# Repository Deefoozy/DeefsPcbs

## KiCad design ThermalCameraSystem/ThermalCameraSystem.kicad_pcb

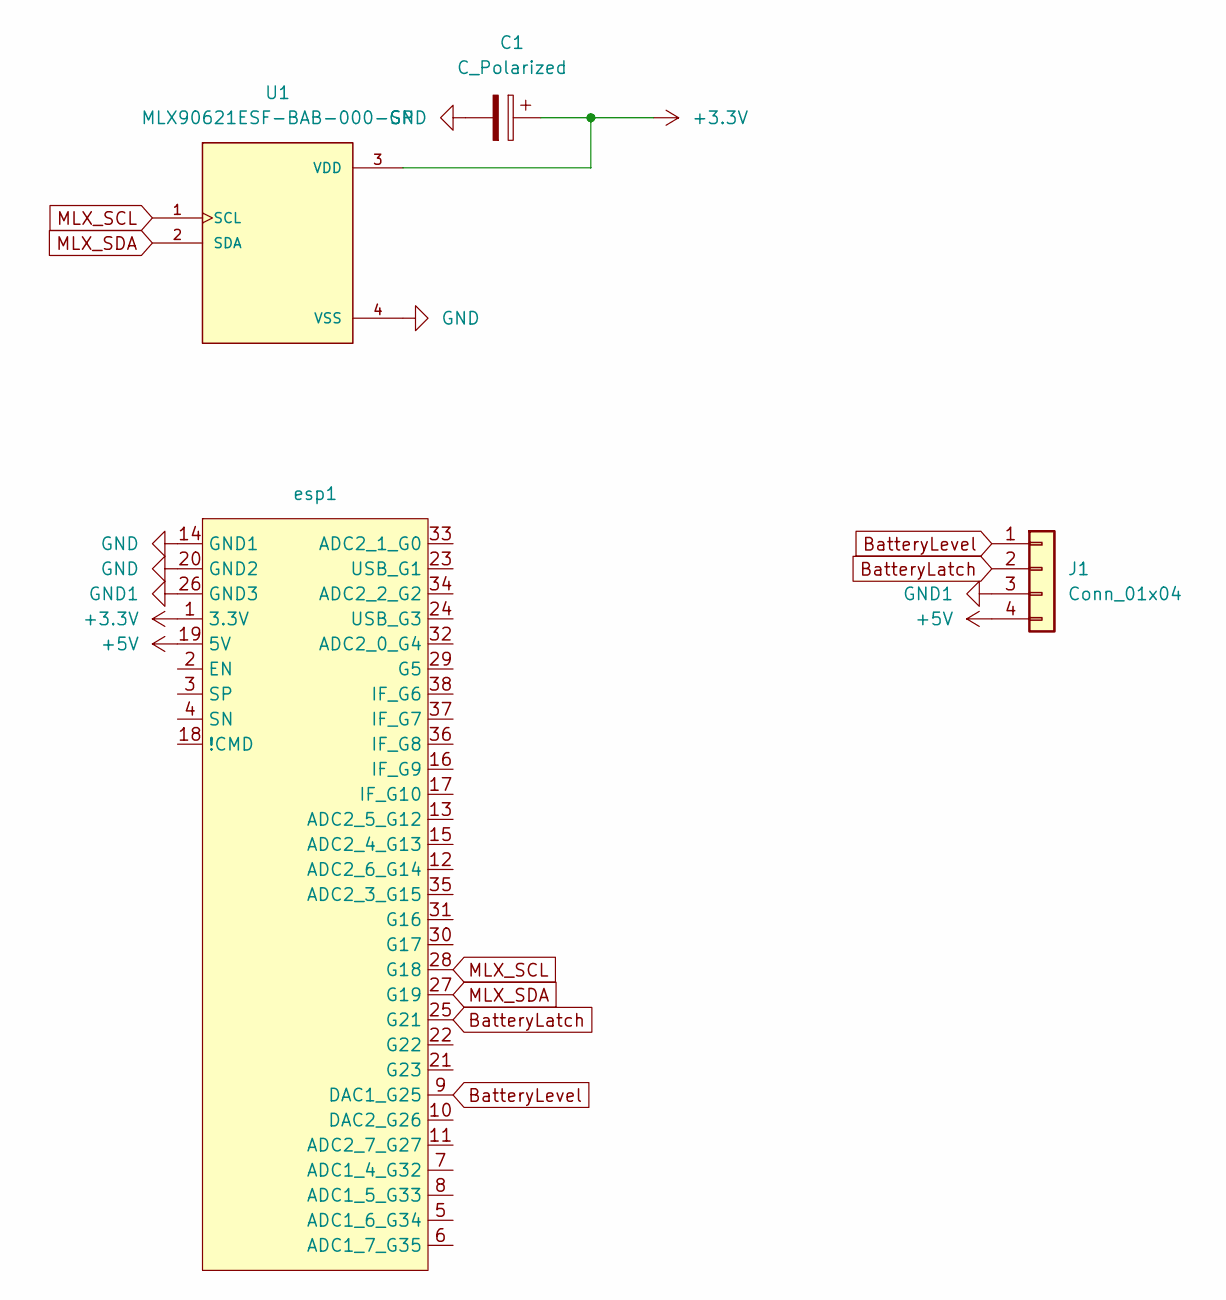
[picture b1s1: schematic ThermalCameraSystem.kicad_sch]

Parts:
C1: C_Polarized; C_Disc_D4.3mm_W1.9mm_P5.00mm
J1: Conn_01x04; PinSocket_1x04_P2.54mm_Vertical
U1: MLX90621ESF-BAB-000-SP; TO292P930H600-4
esp1: AZdelivery_nodemcu_esp32

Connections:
+3.3V: C1.1, U1.3 (VDD), esp1.1 (3.3V)
+5V: J1.4, esp1.19 (5V)
BatteryLatch: J1.2, esp1.25 (G21)
BatteryLevel: J1.1, esp1.9 (DAC1_G25)
GND: C1.2, U1.4 (VSS), esp1.14 (GND1), esp1.20 (GND2)
GND1: J1.3, esp1.26 (GND3)
MLX_SCL: U1.1 (SCL), esp1.28 (G18)
MLX_SDA: U1.2 (SDA), esp1.27 (G19)

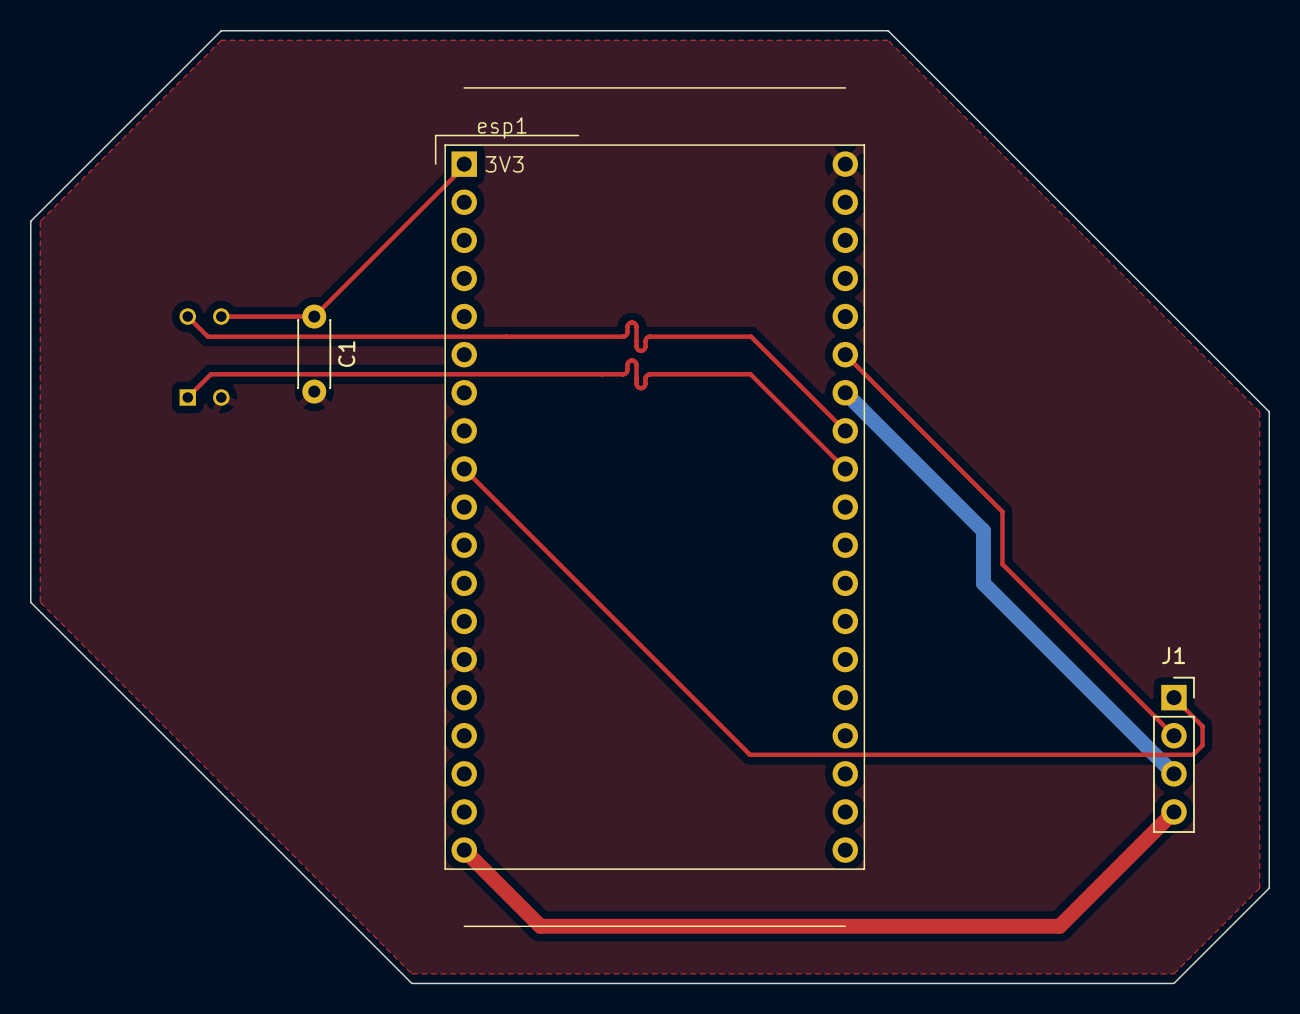
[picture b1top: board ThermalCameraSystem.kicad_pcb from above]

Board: 2 copper layers, 82.5 x 63.5 mm, 4 parts (1 on the bottom side), 8 nets.

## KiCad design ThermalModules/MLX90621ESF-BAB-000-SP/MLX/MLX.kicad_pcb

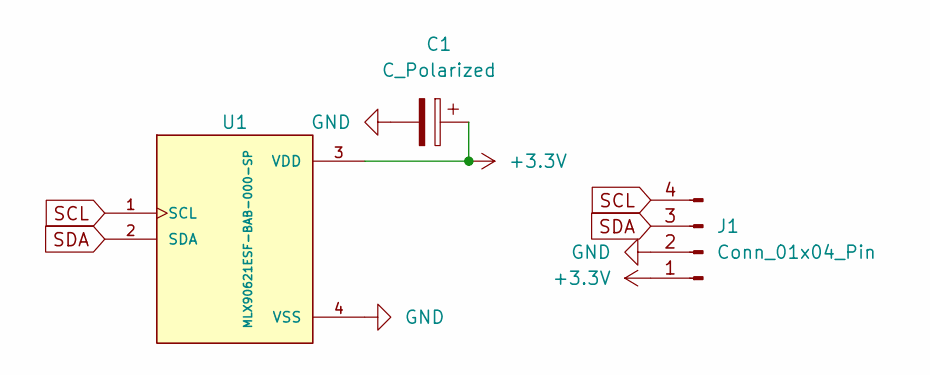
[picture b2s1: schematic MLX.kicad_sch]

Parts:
C1: C_Polarized; C_Disc_D4.3mm_W1.9mm_P5.00mm
J1: Conn_01x04_Pin; PinHeader_1x04_P2.54mm_Vertical
U1: MLX90621ESF-BAB-000-SP; TO254P940H1340-4

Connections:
+3.3V: C1.1, J1.1, U1.3 (VDD)
GND: C1.2, J1.2, U1.4 (VSS)
SCL: J1.4, U1.1 (SCL)
SDA: J1.3, U1.2 (SDA)

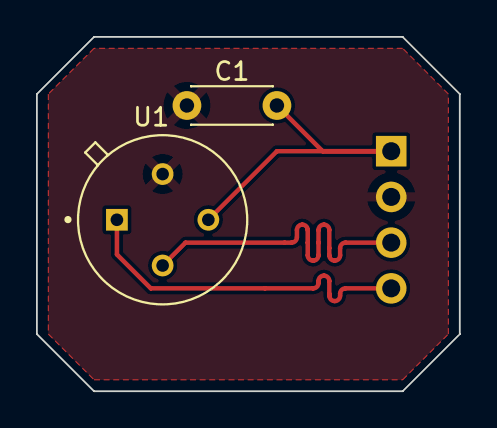
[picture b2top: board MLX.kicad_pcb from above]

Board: 2 copper layers, 23.5 x 19.7 mm, 3 parts (1 on the bottom side), 4 nets.

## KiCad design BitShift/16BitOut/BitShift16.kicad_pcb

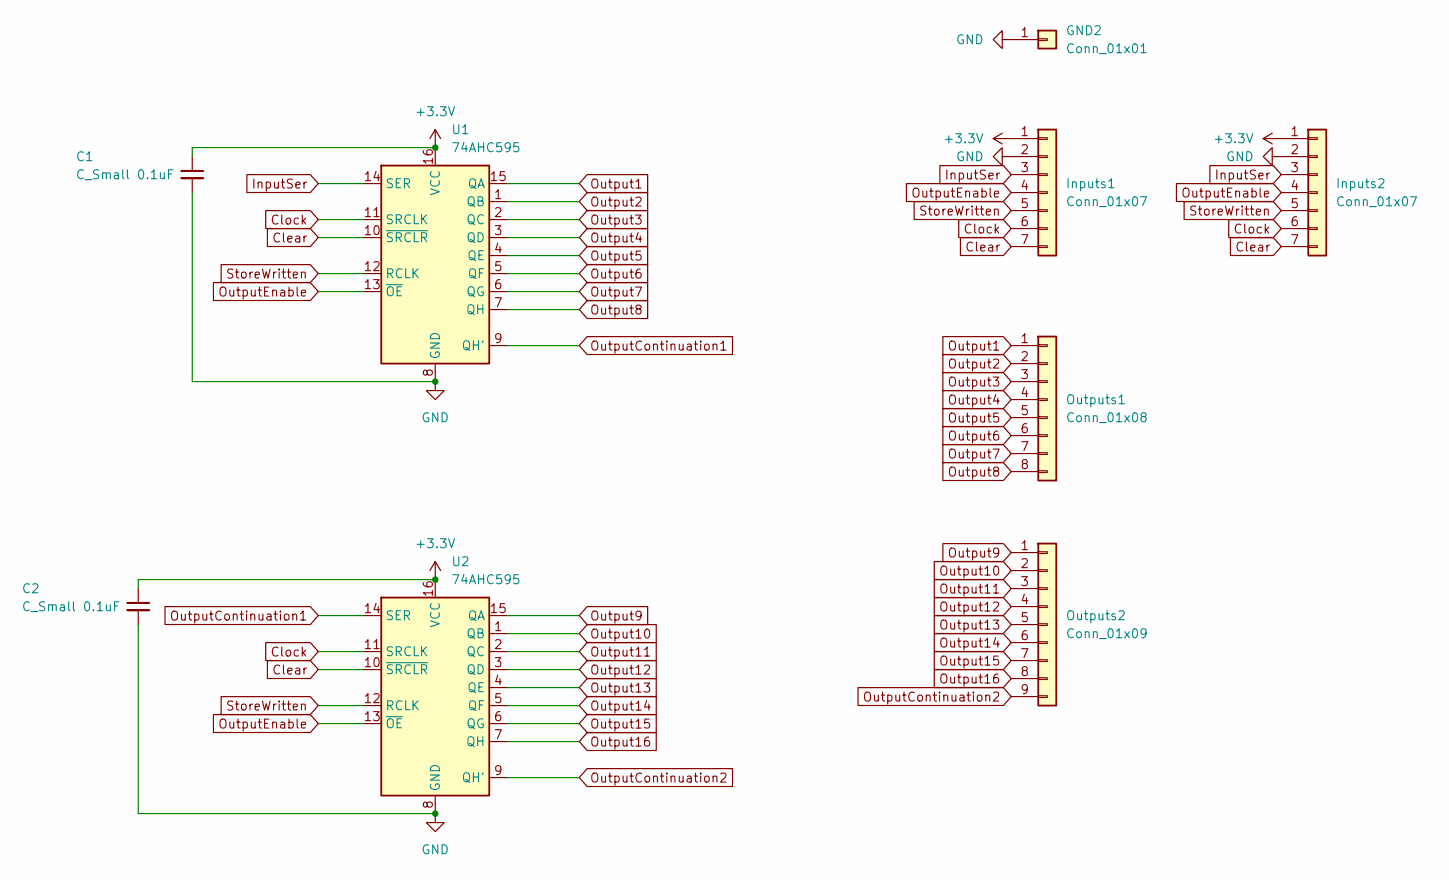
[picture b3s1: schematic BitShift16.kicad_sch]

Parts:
C1, C2: C_Small 0.1uF; C_Disc_D4.3mm_W1.9mm_P5.00mm
GND2: Conn_01x01; PinHeader_1x01_P2.54mm_Vertical
Inputs1: Conn_01x07; PinHeader_1x07_P2.54mm_Vertical
Inputs2: Conn_01x07; JST_EH_S7B-EH_1x07_P2.50mm_Horizontal
Outputs1: Conn_01x08; PinHeader_1x08_P2.54mm_Vertical
Outputs2: Conn_01x09; PinHeader_1x09_P2.54mm_Vertical
U1, U2: 74AHC595; DIP-16_W7.62mm

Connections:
+3.3V: C1.1, C2.1, Inputs1.1, Inputs2.1, U1.16 (VCC), U2.16 (VCC)
Clear: Inputs1.7, Inputs2.7, U1.10 (~SRCLR), U2.10 (~SRCLR)
Clock: Inputs1.6, Inputs2.6, U1.11 (SRCLK), U2.11 (SRCLK)
GND: C1.2, C2.2, GND2.1, Inputs1.2, Inputs2.2, U1.8 (GND), U2.8 (GND)
InputSer: Inputs1.3, Inputs2.3, U1.14 (SER)
Output1: Outputs1.1, U1.15 (QA)
Output2: Outputs1.2, U1.1 (QB)
Output3: Outputs1.3, U1.2 (QC)
Output4: Outputs1.4, U1.3 (QD)
Output5: Outputs1.5, U1.4 (QE)
Output6: Outputs1.6, U1.5 (QF)
Output7: Outputs1.7, U1.6 (QG)
Output8: Outputs1.8, U1.7 (QH)
Output9: Outputs2.1, U2.15 (QA)
Output10: Outputs2.2, U2.1 (QB)
Output11: Outputs2.3, U2.2 (QC)
Output12: Outputs2.4, U2.3 (QD)
Output13: Outputs2.5, U2.4 (QE)
Output14: Outputs2.6, U2.5 (QF)
Output15: Outputs2.7, U2.6 (QG)
Output16: Outputs2.8, U2.7 (QH)
OutputContinuation1: U1.9 (QH'), U2.14 (SER)
OutputContinuation2: Outputs2.9, U2.9 (QH')
OutputEnable: Inputs1.4, Inputs2.4, U1.13 (~OE), U2.13 (~OE)
StoreWritten: Inputs1.5, Inputs2.5, U1.12 (RCLK), U2.12 (RCLK)

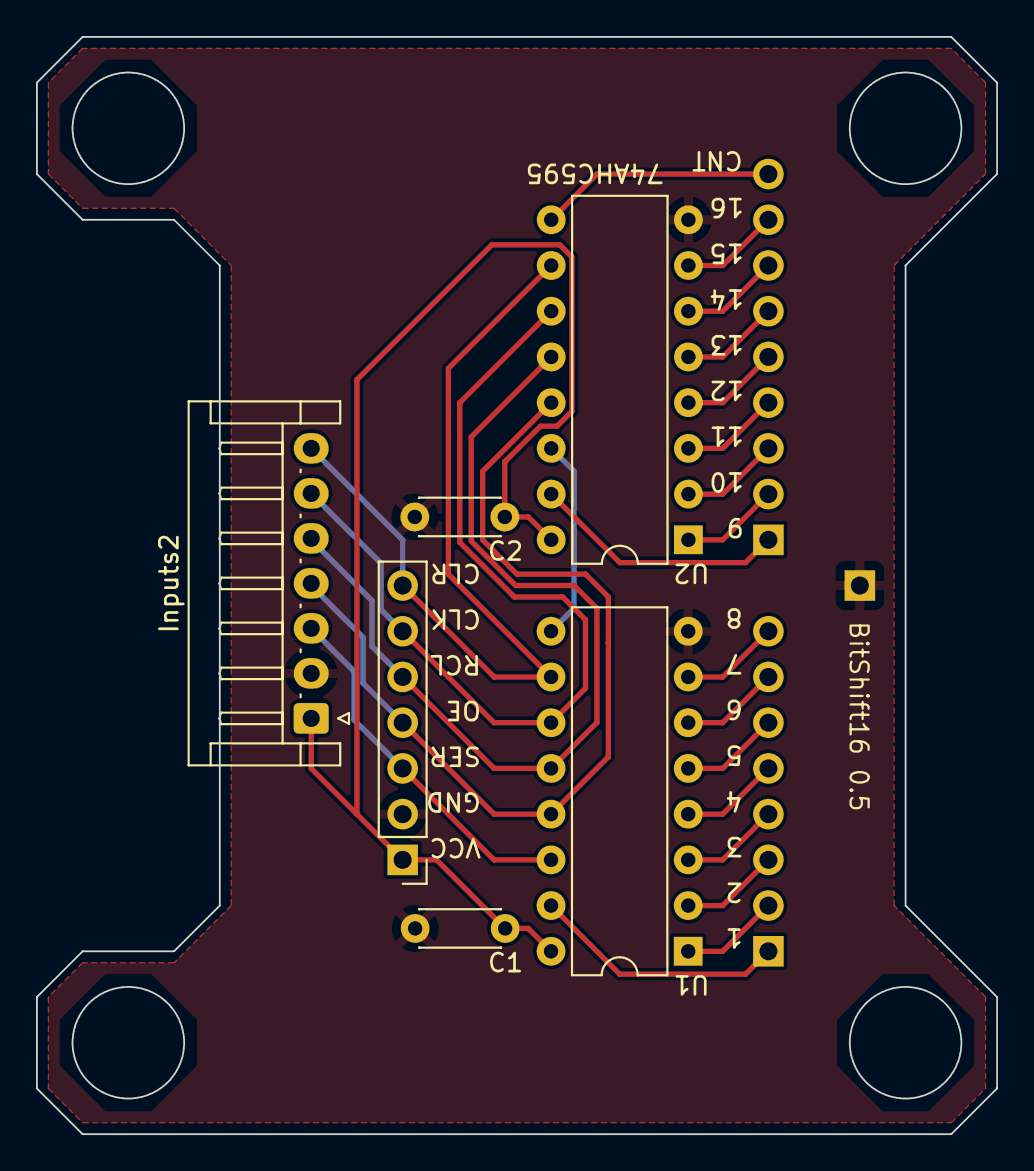
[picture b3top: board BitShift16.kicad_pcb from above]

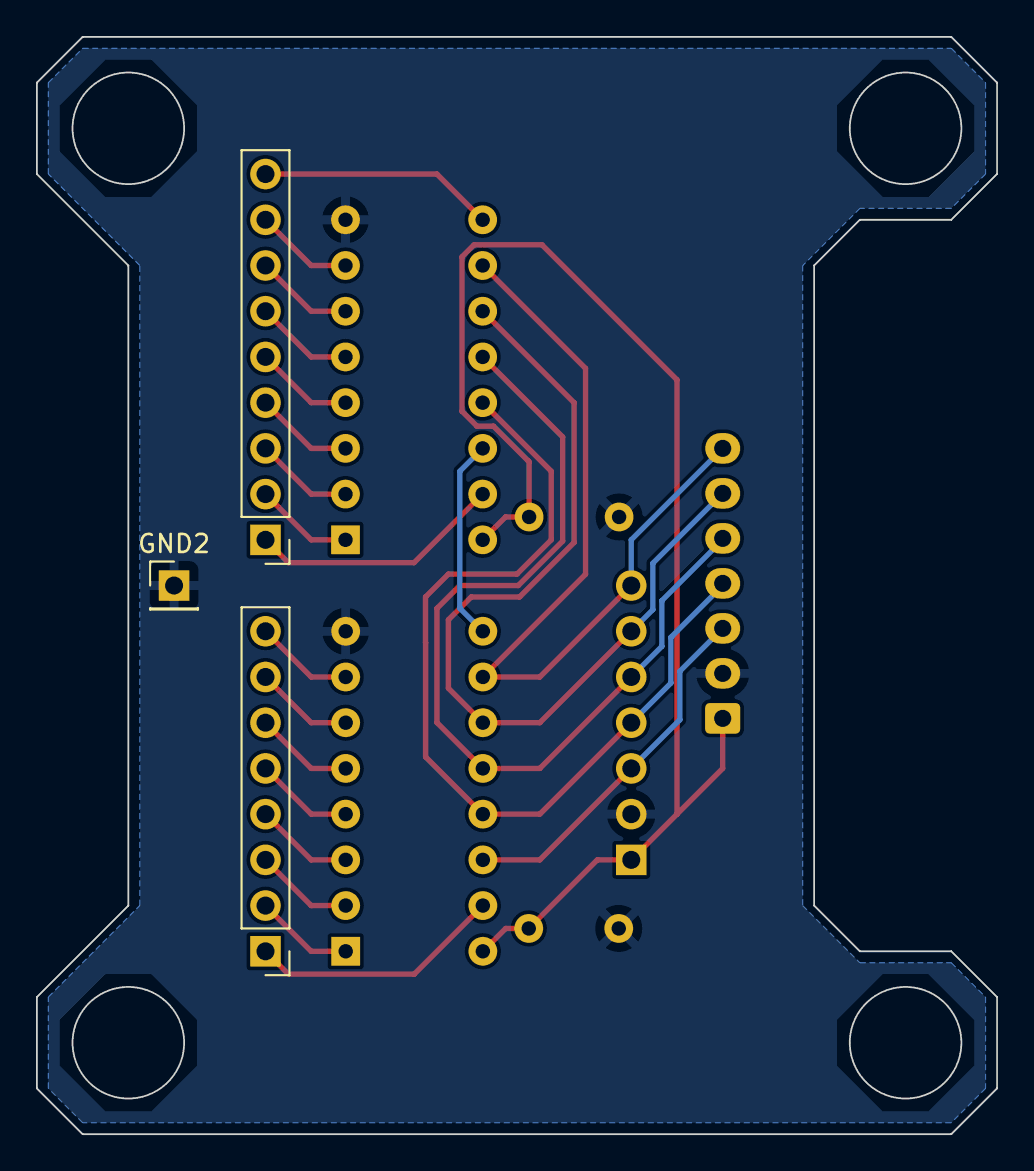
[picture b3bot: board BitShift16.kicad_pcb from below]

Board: 2 copper layers, 53.3 x 61.0 mm, 9 parts (3 on the bottom side), 25 nets.

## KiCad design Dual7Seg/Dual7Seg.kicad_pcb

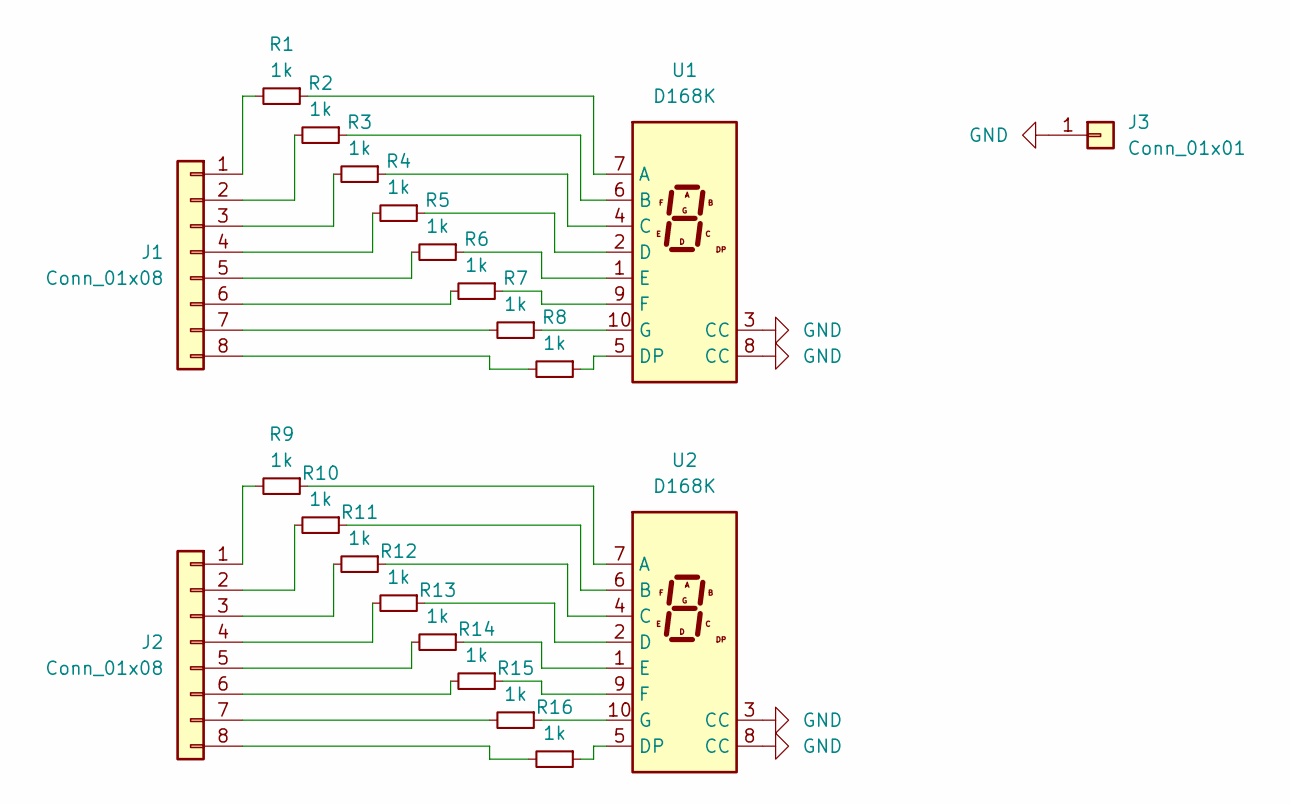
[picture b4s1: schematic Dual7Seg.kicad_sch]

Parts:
J1, J2: Conn_01x08; PinHeader_1x08_P2.54mm_Vertical
J3: Conn_01x01; PinHeader_1x01_P2.54mm_Vertical
R1, R2, R3, R4, R5, R6, R7, R8, R9, R10, R11, R12, R13, R14, R15, R16: 1k; R_Axial_DIN0204_L3.6mm_D1.6mm_P2.54mm_Vertical
U1, U2: D168K; D1X8K

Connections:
GND: J3.1, U1.3 (CC), U1.8 (CC), U2.3 (CC), U2.8 (CC)
unnamed: J1.1, R1.2
unnamed: J1.2, R2.2
unnamed: J1.3, R3.2
unnamed: J1.4, R4.2
unnamed: J1.5, R5.2
unnamed: J1.6, R6.2
unnamed: J1.7, R7.2
unnamed: J1.8, R8.2
unnamed: J2.1, R9.2
unnamed: J2.2, R10.2
unnamed: J2.3, R11.2
unnamed: J2.4, R12.2
unnamed: J2.5, R13.2
unnamed: J2.6, R14.2
unnamed: J2.7, R15.2
unnamed: J2.8, R16.2
unnamed: R1.1, U1.7 (A)
unnamed: R2.1, U1.6 (B)
unnamed: R3.1, U1.4 (C)
unnamed: R4.1, U1.2 (D)
unnamed: R8.1, U1.5 (DP)
unnamed: R5.1, U1.1 (E)
unnamed: R6.1, U1.9 (F)
unnamed: R7.1, U1.10 (G)
unnamed: R9.1, U2.7 (A)
unnamed: R10.1, U2.6 (B)
unnamed: R11.1, U2.4 (C)
unnamed: R12.1, U2.2 (D)
unnamed: R16.1, U2.5 (DP)
unnamed: R13.1, U2.1 (E)
unnamed: R14.1, U2.9 (F)
unnamed: R15.1, U2.10 (G)

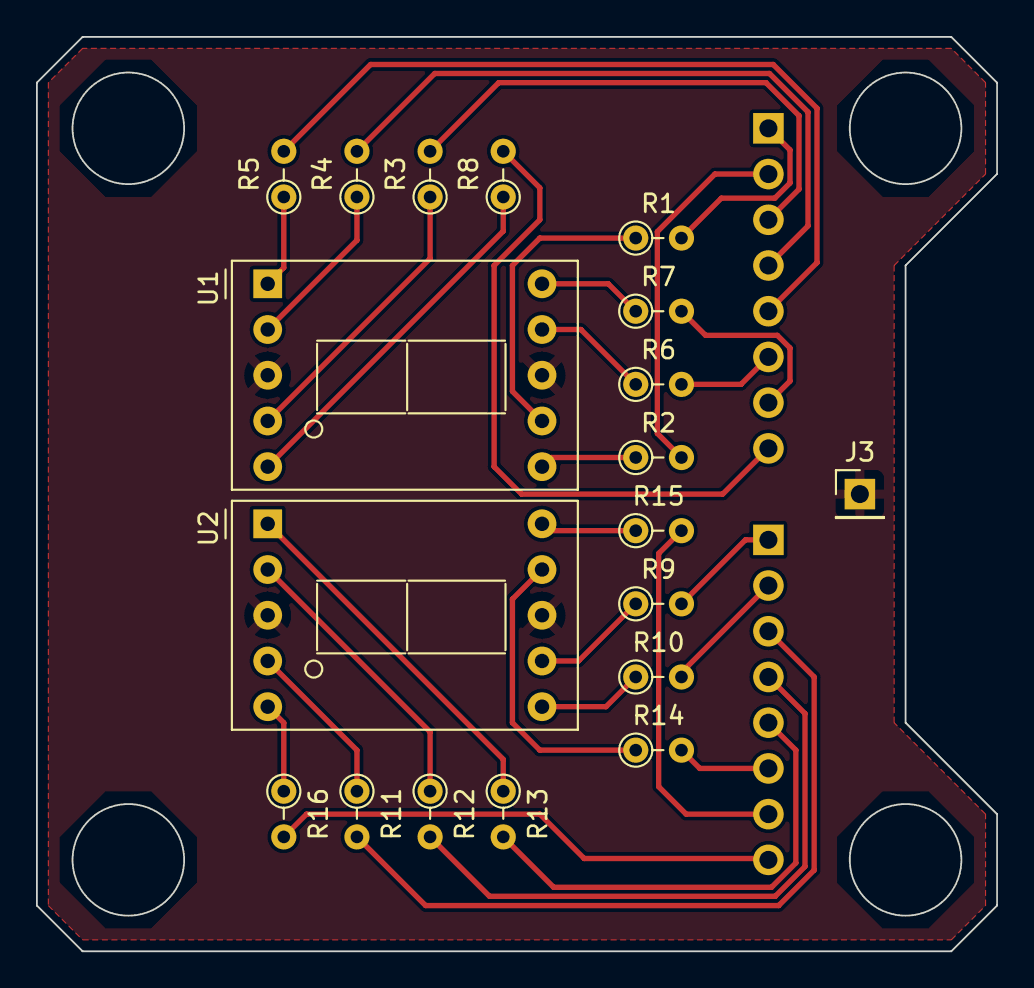
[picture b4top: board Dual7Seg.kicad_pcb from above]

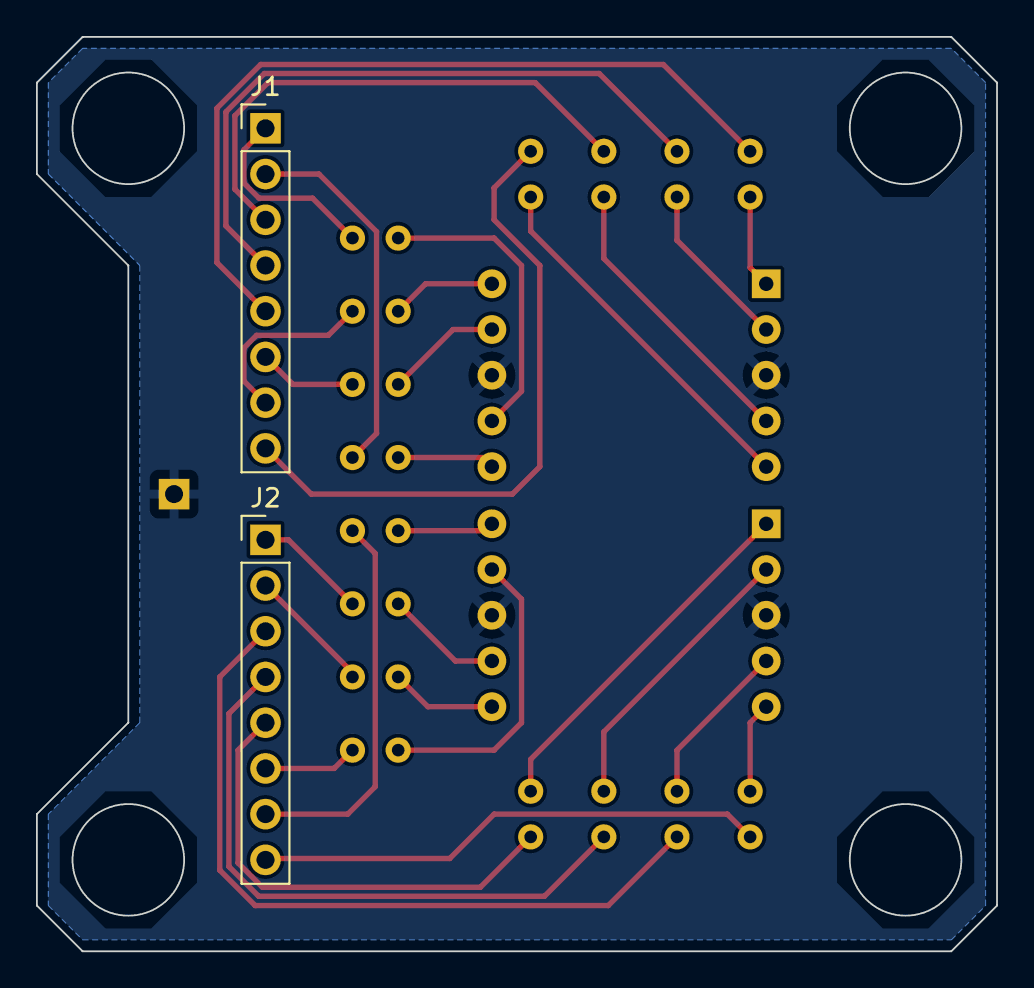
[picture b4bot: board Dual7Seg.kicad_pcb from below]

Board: 2 copper layers, 53.3 x 50.8 mm, 21 parts (2 on the bottom side), 33 nets.

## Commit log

2023-11-19 Added multibitshift
2023-11-19 set up folder structure
2023-11-19 Added dual7seg
2023-11-19 added backups to gitignore
2023-11-19 renamed components
2023-11-19 Updated gitignore
2023-11-19 updated bitshift, dual7 and dualbitshift
2023-11-24 Added some modules
2023-11-24 Added some underlaying files
2024-12-05 Updated main
